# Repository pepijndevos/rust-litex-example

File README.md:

# Rust LiteX Example
An example Rust application that demonstrates [litex-hal](https://github.com/pepijndevos/rust-litex-hal/tree/master).

This application uses [SSD1306](https://github.com/jamwaffles/ssd1306) with [litex-hal](https://github.com/pepijndevos/rust-litex-hal/tree/master)
to run some example code on an [ULX3S](https://radiona.org/ulx3s/) board. It should work on any LiteX SoC with minimal changes.

Info and instructions [on my blog](http://pepijndevos.nl/2020/08/04/a-rust-hal-for-your-litex-fpga-soc.html)

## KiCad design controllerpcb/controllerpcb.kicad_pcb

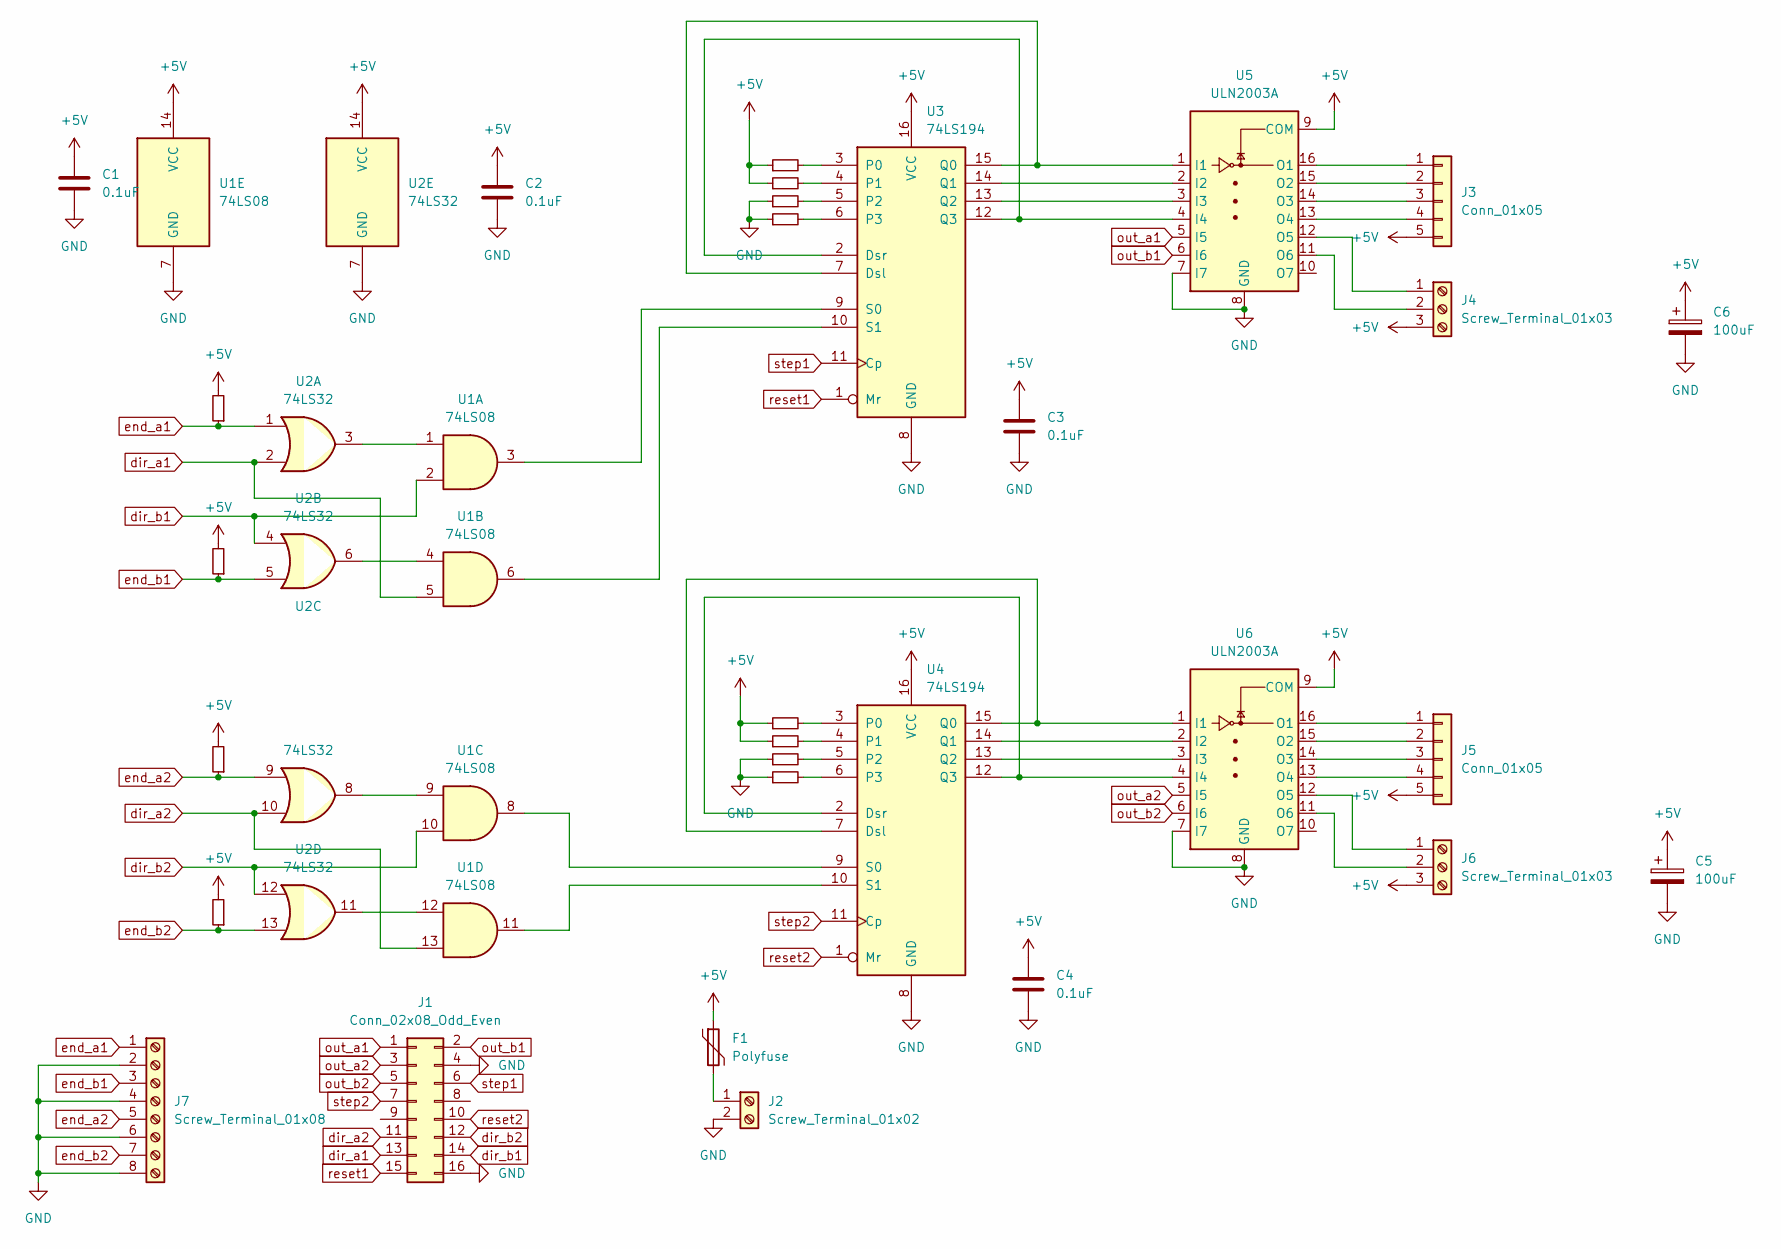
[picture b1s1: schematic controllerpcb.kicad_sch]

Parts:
C1, C2, C3, C4: 0.1uF; C_0603_1608Metric
C5, C6: 100uF; CP_Elec_6.3x5.2; mpn EEEHC1C101XP
F1: Polyfuse; Fuse_1812_4532Metric; mpn 1812L110/24DR
J1: Conn_02x08_Odd_Even; PinHeader_2x08_P2.54mm_Vertical; mpn 61201621621
J2: Screw_Terminal_01x02; TerminalBlock_Phoenix_MKDS-1,5-2_1x02_P5.00mm_Horizontal; mpn 1935161
J3, J5: Conn_01x05; JST_XH_B5B-XH-AM_1x05_P2.50mm_Vertical; mpn B5B-XH-A(LF)(SN)
J4, J6: Screw_Terminal_01x03; TerminalBlock_Phoenix_MPT-0,5-3-2.54_1x03_P2.54mm_Horizontal; mpn OSTVN03A150
J7: Screw_Terminal_01x08; TerminalBlock_Phoenix_MPT-0,5-8-2.54_1x08_P2.54mm_Horizontal; mpn OSTVN08A150
R1, R2, R3, R4, R5, R9: 1K; R_0603_1608Metric
R6, R7, R8, R10, R11, R12: 1k; R_0603_1608Metric
U1: 74LS08; SOIC-14_3.9x8.7mm_P1.27mm
U2: 74LS32; SOIC-14_3.9x8.7mm_P1.27mm
U3, U4: 74LS194; SOIC-16_3.9x9.9mm_P1.27mm; mpn CD74HC194M
U5, U6: ULN2003A; SOIC-16_3.9x9.9mm_P1.27mm

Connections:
+5V: C1.1, C2.1, C3.1, C4.1, C5.1, C6.1, F1.1, J3.5, J4.3, J5.5, J6.3, R1.2, R2.2, R3.2, R4.2, R5.1, R6.1, R9.1, R10.1, U1.14 (VCC), U2.14 (VCC), U3.16 (VCC), U4.16 (VCC), U5.9 (COM), U6.9 (COM)
GND: C1.2, C2.2, C3.2, C4.2, C5.2, C6.2, J1.4, J1.16, J2.2, J7.2, J7.4, J7.6, J7.8, R7.1, R8.1, R11.1, R12.1, U1.7 (GND), U2.7 (GND), U3.8 (GND), U4.8 (GND), U5.7 (I7), U5.8 (GND), U6.7 (I7), U6.8 (GND)
unnamed: F1.2, J2.1
unnamed: J3.1, U5.16 (O1)
unnamed: J3.2, U5.15 (O2)
unnamed: J3.3, U5.14 (O3)
unnamed: J3.4, U5.13 (O4)
unnamed: J4.1, U5.12 (O5)
unnamed: J4.2, U5.11 (O6)
unnamed: J5.1, U6.16 (O1)
unnamed: J5.2, U6.15 (O2)
unnamed: J5.3, U6.14 (O3)
unnamed: J5.4, U6.13 (O4)
unnamed: J6.1, U6.12 (O5)
unnamed: J6.2, U6.11 (O6)
unnamed: R5.2, U3.3 (P0)
unnamed: R6.2, U3.4 (P1)
unnamed: R7.2, U3.5 (P2)
unnamed: R8.2, U3.6 (P3)
unnamed: R9.2, U4.3 (P0)
unnamed: R10.2, U4.4 (P1)
unnamed: R11.2, U4.5 (P2)
unnamed: R12.2, U4.6 (P3)
unnamed: U1.1, U2.3
unnamed: U1.3, U3.9 (S0)
unnamed: U1.4, U2.6
unnamed: U1.6, U3.10 (S1)
unnamed: U1.8, U4.9 (S0)
unnamed: U1.9, U2.8
unnamed: U1.11, U4.10 (S1)
unnamed: U1.12, U2.11
unnamed: U3.2 (Dsr), U3.12 (Q3), U5.4 (I4)
unnamed: U3.13 (Q2), U5.3 (I3)
unnamed: U3.14 (Q1), U5.2 (I2)
unnamed: U3.7 (Dsl), U3.15 (Q0), U5.1 (I1)
unnamed: U4.2 (Dsr), U4.12 (Q3), U6.4 (I4)
unnamed: U4.13 (Q2), U6.3 (I3)
unnamed: U4.14 (Q1), U6.2 (I2)
unnamed: U4.7 (Dsl), U4.15 (Q0), U6.1 (I1)
dir_a1: J1.13, U1.5, U2.2
dir_a2: J1.11, U1.13, U2.10
dir_b1: J1.14, U1.2, U2.4
dir_b2: J1.12, U1.10, U2.12
end_a1: J7.1, R1.1, U2.1
end_a2: J7.5, R3.1, U2.9
end_b1: J7.3, R2.1, U2.5
end_b2: J7.7, R4.1, U2.13
out_a1: J1.1, U5.5 (I5)
out_a2: J1.3, U6.5 (I5)
out_b1: J1.2, U5.6 (I6)
out_b2: J1.5, U6.6 (I6)
reset1: J1.15, U3.1 (Mr)
reset2: J1.10, U4.1 (Mr)
step1: J1.6, U3.11 (Cp)
step2: J1.7, U4.11 (Cp)

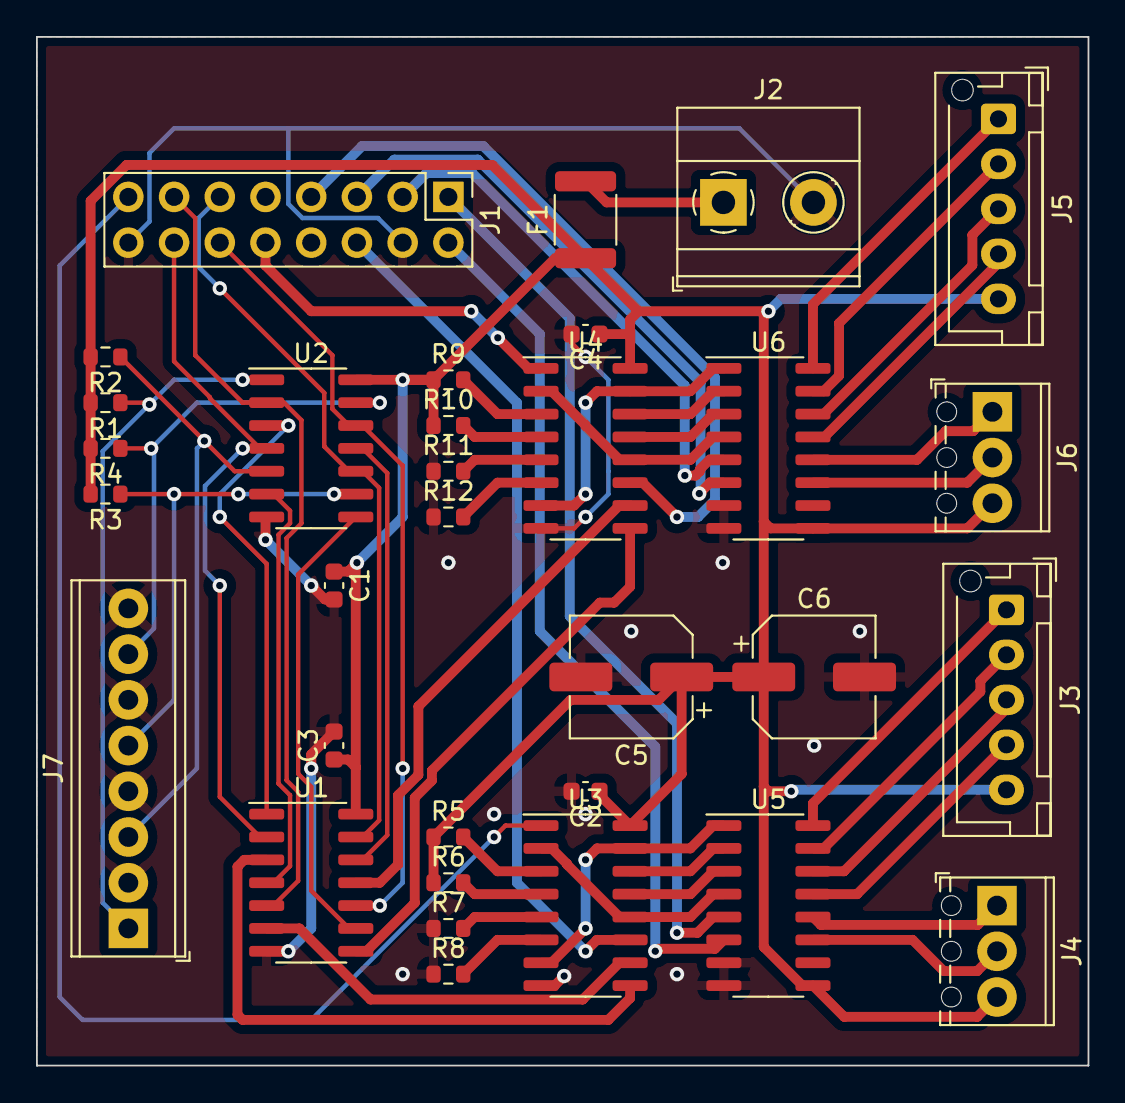
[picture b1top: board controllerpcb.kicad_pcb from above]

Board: 2 copper layers, 58.4 x 57.2 mm, 32 parts (0 on the bottom side), 55 nets.

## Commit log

2020-08-05 Create LICENSE
2022-04-27 update example
2022-05-19 stepper motor driver
2022-05-31 add WIP controller PCB
2022-06-02 pcb v1
2022-06-15 trying new pcb
2022-06-15 test in simulation
2022-06-16 fix stepper reset stuff
2022-06-16 reduce stepper luts
